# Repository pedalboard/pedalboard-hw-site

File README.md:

# pedalboard-hw-site

Source code for github pages avalilable from https://pedalboard.github.io/pedalboard-hw-site

This is mostly generated. Do not edit directly!

* latest is generated from main
* latest-x is generated from branch x
* vX.Y.Z are the released versions
* stable points to the current stable release

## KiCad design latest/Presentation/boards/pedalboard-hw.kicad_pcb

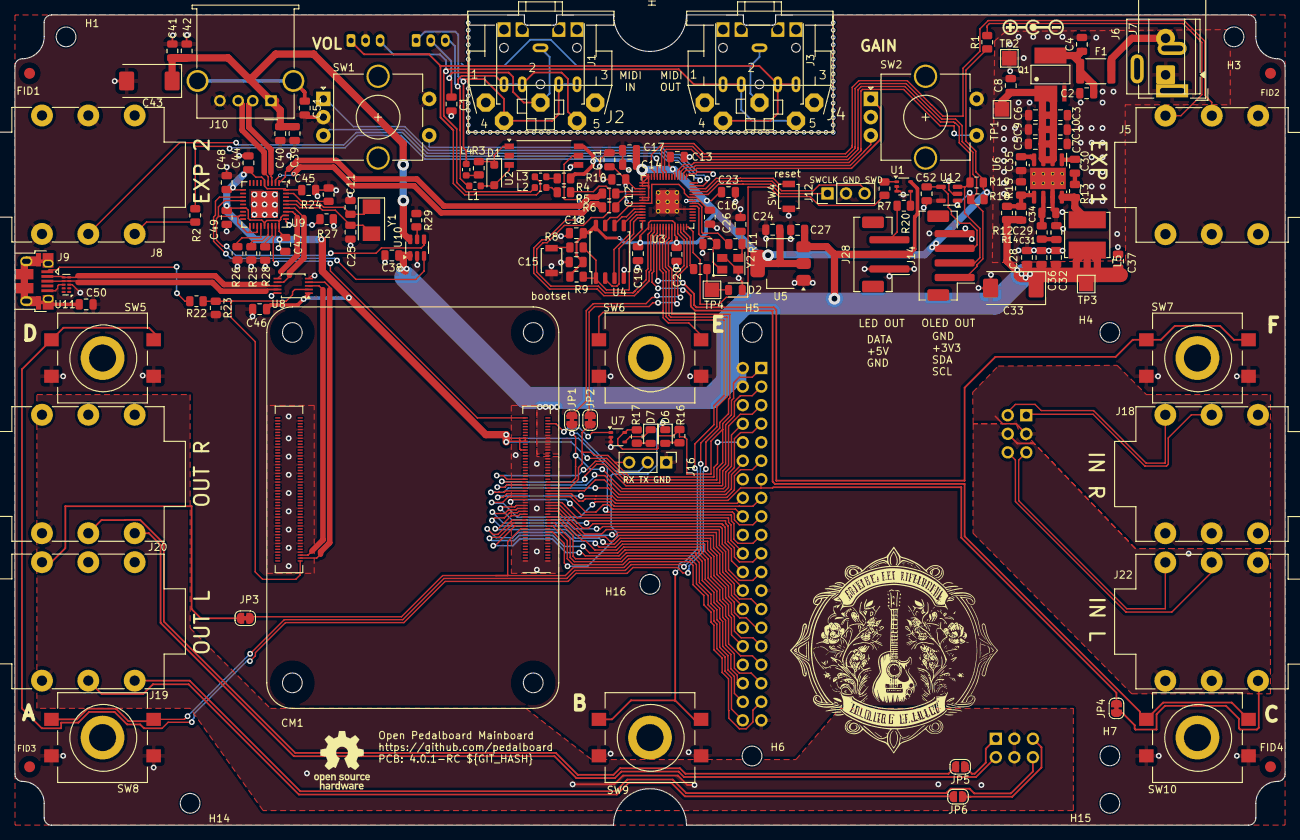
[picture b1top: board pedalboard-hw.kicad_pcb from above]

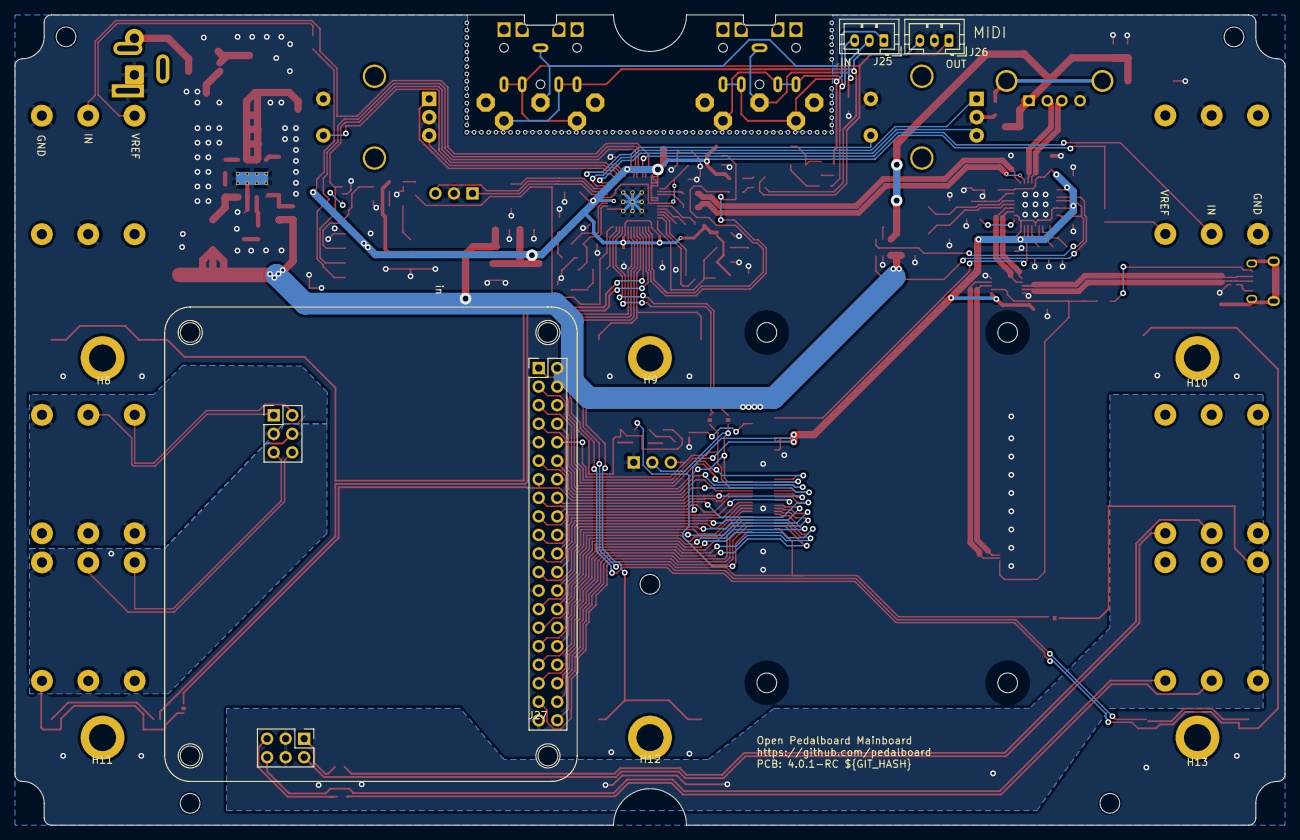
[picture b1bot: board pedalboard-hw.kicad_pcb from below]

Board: 2 copper layers, 174.0 x 111.0 mm, 169 parts (9 on the bottom side), 142 nets.

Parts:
C1, C13, C15, C16, C17, C18, C19, C20, C21, C23, C30, C35, C46, C47, C48, C49, C52: 100n; C_0805_2012Metric
C2, C3, C4, C5, C6, C7, C8, C9, C10, C24, C27, C28, C32, C36, C37, C38, C39, C40, C41, C42, C44, C45: 10u; C_0805_2012Metric
C11, C25: 18p; C_0805_2012Metric
C12, C14: 1u; C_0805_2012Metric
C22, C26: 15p; C_0805_2012Metric
C29, C34, C50, C51: 1n; C_0805_2012Metric
C31: 1.2n; C_0805_2012Metric
C33, C43: 100u; CP_EIA-7343-31_Kemet-D
CM1: CM4; Raspberry-Pi-4-Compute-Module
D1: SM4007; D_SOD-123F
D2, D6: LED Y; LED_0805_2012Metric
D7: LED R; LED_0805_2012Metric
F1: Polyfuse 1.8A; Fuse_1812_4532Metric
FID1, FID2, FID3, FID4: Fiducial; Fiducial_1.5mm_Mask3mm
H1, H3, H4, H5, H6, H7, H14, H15, H16: MountingHole; MountingHole_2.7mm_M2.5_DIN965
H2: Midi Bites; MIDI bites
H8, H9, H10, H11, H12, H13: Spacer; WA-SMSI_M2.5
J1, J3: Jack 3.5mm; Jack_3.5mm_CUI_SJ1-3525N_Horizontal
J2, J4: DIN5; CP-2350
J5, J8, J18, J19, J20, J22: Jack 6.35mm; Jack_6.35mm_Horizontal
J6: Screw_Terminal_01x02; TerminalBlock_Phoenix_MKDS-1,5-2_1x02_P5.00mm_Horizontal
J7: Barrel_Jack_MountingPin; BarrelJack_Wuerth_6941xx301002
J9: USB_OTG; USB_Micro-B_Amphenol_10103594-0001LF_Horizontal
J10: USB_A; USB_A_Molex_67643_Horizontal
J12, J16: Debug; PinHeader_1x03_P2.54mm_Vertical
J14: JST PH 4; JST_PH_B4B-PH-SM4-TB_1x04-1MP_P2.00mm_Vertical
J25, J26: JST PH 3; JST_PH_B3B-PH-K_1x03_P2.00mm_Vertical
J27: Pedalboard Soundcard; Pedalboard_Soundcard
J28: JST PH 3; JST_PH_B3B-PH-SM4-TB_1x03-1MP_P2.00mm_Vertical
JP1, JP2, JP3, JP4: SJP; SolderJumper-2_P1.3mm_Bridged_RoundedPad1.0x1.5mm
JP5, JP6: SJP; SolderJumper-2_P1.3mm_Open_RoundedPad1.0x1.5mm
L1, L2, L3, L4: 120_100MHz; L_0603_1608Metric
L5: SRN6045TA-3R3Y; L_Bourns_SRN6045TA
Q1: FDS4435BZ; SO08-E3
R1, R2, R8, R11, R16: 1K; R_0805_2012Metric
R3, R7, R20: 220R; R_0805_2012Metric
R4: 33R; R_0805_2012Metric
R5, R13: 10R; R_0805_2012Metric
R6, R10: 27R; R_0805_2012Metric
R9: DNF; R_0805_2012Metric
R12, R24: 12K; R_0805_2012Metric
R14: 20K; R_0805_2012Metric
R15, R17, R21, R22, R23: 2K2; R_0805_2012Metric
R18, R19: 3K9; R_0805_2012Metric
R25, R26, R27, R28, R29: 36K; R_0805_2012Metric
SW1, SW2: 24P/R 24mm; RotaryEncoder_Alps_EC11E-Switch_Vertical_H20mm_CircularMoun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
SW3, SW4: Micro Button; SW_SPST_B3U-1000P
SW5, SW6, SW7, SW8, SW9, SW10: Tactile Button; SW_PUSH-12mm_Wuerth
SYM1: Logo_Open_Hardware_Small; OSHW-Logo_7.5x8mm_SilkScreen
TP1, TP2, TP3, TP4: TestPoint; TestPoint_Pad_2.0x2.0mm
U1, U7: 74AHCT1G32SE-7; SOT-353_SC-70-5
U2: TLP2761; SO-6L_10x3.84mm_P1.27mm
U3: RP2040; RP2040-QFN-56
U4: W25Q128JVS; SOIC-8_5.23x5.23mm_P1.27mm
U5: NCP1117-3.3_SOT223; SOT-223-3_TabPin2
U6: AP64501SP-13; SOIC-8-1EP_3.9x4.9mm_P1.27mm_EP2.95x4.9mm_Mask2.71x3.4mm_Th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
U8: FSUSB42MUX; TSSOP-10_3x3mm_P0.5mm
U9: USB2514B_Bi; QFN-36-1EP_6x6mm_P0.5mm_EP3.7x3.7mm
U10: AP2553W6; SOT-23-6
U11: TPD4EUSB30; USON-10_2.5x1.0mm_P0.5mm
U12: AT24CS01-STUM; SOT-23-5
Y1: Crystal_Small; Crystal_SMD_5032-2Pin_5.0x3.2mm
Y2: ABM8-272-T3; ABM8-272-T3_ABR

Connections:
+1V1: C12.1, C16.1, C21.1, U3.23 (DVDD), U3.45 (VREG_VOUT), U3.50 (DVDD)
+3V3: C13.1, C14.1, C15.1, C17.1, C18.1, C19.1, C20.1, C23.1, C24.1, C52.1, J14.3, R1.1, R2.1, R4.1, R9.1, R18.1, R19.1, U2.6 (VDD), U3.1 (IOVDD), U3.10 (IOVDD), U3.22 (IOVDD), U3.33 (IOVDD), U3.42 (IOVDD), U3.43 (ADC_AVDD), U3.44 (VREG_IN), U3.48 (USB_VDD), U3.49 (IOVDD), U4.8 (VCC), U5.2 (VO), U12.4 (VCC)
+5VP: C27.1, C28.1, C29.1, C32.1, C33.1, C36.1, C37.1, C38.1, CM1.77 (+5v_(Input)), CM1.79 (+5v_(Input)), CM1.81 (+5v_(Input)), CM1.83 (+5v_(Input)), CM1.85 (+5v_(Input)), CM1.87 (+5v_(Input)), J27.2 (5V), J27.4 (5V), J28.2, L5.2, R12.1, TP3.1, U1.5 (VCC), U5.3 (VI), U10.1 (IN)
/Audio/CM4_3V: C44.1, C45.1, C46.1, C47.1, C48.1, C49.1, CM1.78 (GPIO_VREF(1.8v/3.3v_Input)), CM1.84 (+3.3v_(Output)), CM1.86 (+3.3v_(Output)), J27.1 (3V3), J27.17 (3V3), R16.2, R17.2, U7.5 (VCC), U8.1 (VCC), U9.5 (VDDA33), U9.10 (VDDA33), U9.15 (VDD33), U9.23 (VDD33), U9.27 (VBUS_DET), U9.29 (VDDA33), U9.36 (VDDA33)
/Audio/CM4_GPIO4: CM1.54 (GPIO4), J27.7 (GCLK0/GPIO4)
/Audio/CM4_GPIO5: CM1.34 (GPIO5), J27.29 (GCLK1/GPIO5)
/Audio/CM4_GPIO6: CM1.30 (GPIO6), J27.31 (GCLK2/GPIO6)
/Audio/CM4_GPIO7: CM1.37 (GPIO7), J27.26 (~CE1/GPIO7)
/Audio/CM4_GPIO8: CM1.39 (GPIO8), J27.24 (~CE0/GPIO8)
/Audio/CM4_GPIO9: CM1.40 (GPIO9), J27.21 (MISO0/GPIO9)
/Audio/CM4_GPIO10: CM1.44 (GPIO10), J27.19 (MOSI0/GPIO10)
/Audio/CM4_GPIO11: CM1.38 (GPIO11), J27.23 (SCLK0/GPIO11)
/Audio/CM4_GPIO12: CM1.31 (GPIO12), J27.32 (PWM0/GPIO12)
/Audio/CM4_GPIO13: CM1.28 (GPIO13), J27.33 (PWM1/GPIO13)
/Audio/CM4_GPIO16: CM1.29 (GPIO16), J27.36 (GPIO16)
/Audio/CM4_GPIO17: CM1.50 (GPIO17), J27.11 (GPIO17)
/Audio/CM4_GPIO22: CM1.46 (GPIO22), J27.15 (GPIO22)
/Audio/CM4_GPIO23: CM1.47 (GPIO23), J27.16 (GPIO23)
/Audio/CM4_GPIO24: CM1.45 (GPIO24), J27.18 (GPIO24)
/Audio/CM4_GPIO25: CM1.41 (GPIO25), J27.22 (GPIO25)
/Audio/CM4_ID_SC: CM1.35 (ID_SC), J27.28 (ID_SC/GPIO1)
/Audio/CM4_ID_SD: CM1.36 (ID_SD), J27.27 (ID_SD/GPIO0)
/Audio/CM4_LED_ACT: CM1.21 (PI_nLED_Activity), D6.1 (K)
/Audio/CM4_LED_PWR: CM1.95 (nPI_LED_PWR), U7.1 (A)
/Audio/GND_in_L: J22.RN, J22.S, J22.TN, J27.44 (in_GND)
/Audio/GND_in_R: J18.RN, J18.S, J18.TN, J27.43 (in_GND)
/Audio/GND_out: J19.S, J20.S, J27.49 (out_GND), J27.50 (out_GND)
/Audio/INT_MIDI_RX: CM1.51 (GPIO15), J16.3, J27.10 (GPIO15/RXD), JP2.1 (A)
/Audio/INT_MIDI_TX: CM1.55 (GPIO14), J16.2, J27.8 (GPIO14/TXD), JP1.1 (A)
/Audio/audio_in_stereo: CM1.48 (GPIO27), J27.13 (GPIO27), JP4.2 (B)
/Audio/audio_out_stereo: CM1.24 (GPIO26), J27.37 (GPIO26), JP3.2 (B)
/Audio/audio_pcm_clk: CM1.49 (GPIO18), J27.12 (GPIO18/PWM0)
/Audio/audio_pcm_din: CM1.27 (GPIO20), J27.38 (GPIO20/MOSI1)
/Audio/audio_pcm_dout: CM1.25 (GPIO21), J27.40 (GPIO21/SCLK1)
/Audio/audio_pcm_fs: CM1.26 (GPIO19), J27.35 (GPIO19/MISO1)
/Audio/conf_i2c_scl: CM1.56 (GPIO3), J27.5 (SCL/GPIO3)
/Audio/conf_i2c_sda: CM1.58 (GPIO2), J27.3 (SDA/GPIO2)
/Audio/in_L+: J22.T, J27.45 (in_L+)
/Audio/in_L-: J22.R, J27.46 (in_L-)
/Audio/in_R+: J18.T, J27.42 (in_R+)
/Audio/in_R-: J18.R, J27.41 (in_R-)
/Audio/nEXTRST: CM1.100 (nEXTRST), U9.26 (RESET_N)
/Connectivity/USB_CM_N: CM1.103 (USB2_N), U8.4 (D-)
/Connectivity/USB_CM_P: CM1.105 (USB2_P), U8.3 (D+)
/Connectivity/USB_D_N: J9.2 (D-), U8.8 (HSD2-), U11.5 (D2-)
/Connectivity/USB_D_P: J9.3 (D+), U8.9 (HSD2+), U11.4 (D2+)
/Connectivity/USB_OUT_N: J10.2 (D-), U9.3 (USBDM_DN2/PRT_DIS_M2)
/Connectivity/USB_OUT_P: J10.3 (D+), U9.4 (USBDP_DN2/PRT_DIS_P2)
/Connectivity/USB_RP_N: R10.1, U9.1 (USBDM_DN1/PRT_DIS_M1)
/Connectivity/USB_RP_P: R6.1, U9.2 (USBDP_DN1/PRT_DIS_P1)
/Connectivity/USB_UP_N: U8.6 (HSD1-), U9.30 (USBDM_UP)
/Connectivity/USB_UP_P: U8.7 (HSD1+), U9.31 (USBDP_UP)
/Connectivity/VBUS: C39.1, C40.1, C41.1, C42.1, C43.1, J10.1 (VBUS), U10.6 (OUT)
/Connectivity/nOCS1: U9.13 (OCS_N1), U9.17 (OCS_N2), U9.19 (OCS_N3), U9.21 (OCS_N4), U10.4 (nFault)
/LEDs/RGB_DATA: R7.1, U3.14 (GPIO11)
/MIDI/A_EXP1: J5.R, U3.40 (GPIO28_ADC2)
/MIDI/A_EXP2: J8.R, U3.39 (GPIO27_ADC1)
/MIDI/EXT_MIDI_RX: U2.5 (VO), U3.3 (GPIO1)
/MIDI/EXT_MIDI_TX: R5.2, U3.2 (GPIO0)
/MIDI/I2C_SCL: J14.1, R18.2, U3.37 (GPIO25), U12.1 (SCL)
/MIDI/I2C_SDA: J14.2, R19.2, U3.36 (GPIO24), U12.3 (SDA)
/MIDI/QSPI_SCLK: U3.52 (QSPI_SCLK), U4.6 (CLK)
/MIDI/QSPI_SD0: U3.53 (QSPI_SD0), U4.5 (DI(IO0))
/MIDI/QSPI_SD1: U3.55 (QSPI_SD1), U4.2 (DO(IO1))
/MIDI/QSPI_SD2: U3.54 (QSPI_SD2), U4.3 (IO2)
/MIDI/QSPI_SD3: U3.51 (QSPI_SD3), U4.7 (IO3)
/MIDI/QSPI_SS: R8.2, R9.2, U3.56 (QSPI_SS), U4.1 (~CS)
/MIDI/ROT_GAIN_A: SW2.A, U3.30 (GPIO19)
/MIDI/ROT_GAIN_B: SW2.B, U3.31 (GPIO20)
/MIDI/ROT_VOL_A: SW1.A, U3.27 (GPIO16)
/MIDI/ROT_VOL_B: SW1.B, U3.28 (GPIO17)
/MIDI/SWCLK: J12.1, U3.24 (SWCLK)
/MIDI/SWD: J12.3, U3.25 (SWD)
/MIDI/SW_A: SW8.1, U3.8 (GPIO6)
/MIDI/SW_B: SW9.1, U3.7 (GPIO5)
/MIDI/SW_C: SW10.1, U3.4 (GPIO2)
/MIDI/SW_D: SW5.1, U3.9 (GPIO7)
/MIDI/SW_E: SW6.1, U3.6 (GPIO4)
/MIDI/SW_F: SW7.1, U3.5 (GPIO3)
/MIDI/SW_GAIN: SW2.S1, U3.32 (GPIO21)
/MIDI/SW_VOL: SW1.S1, U3.29 (GPIO18)
/MIDI/XIN: C22.1, U3.20 (XIN), Y2.1
/MIDI/XOUT: R11.1, U3.21 (XOUT)
/MIDI/~USB_BOOT: R8.1, SW3.2
/Power Supply/fused: C2.1, C4.1, F1.2, Q1.5-8
/Power Supply/polarity_checked: C3.1, C5.1, C6.1, C7.1, C8.1, C9.1, C10.1, Q1.1-3, TP1.1, U6.2 (VIN), U6.3 (EN)
/Power Supply/switch: L5.1, R13.1, U6.8 (SW)
/Power Supply/unfused: F1.1, J6.2, J7.2
GND: C1.2, C2.2, C3.2, C4.2, C5.2, C6.2, C7.2, C8.2, C9.2, C10.2, C11.2, C12.2, C13.2, C14.2, C15.2, C16.2, C17.2, C18.2, C19.2, C20.2, C21.2, C22.2, C23.2, C24.2, C25.2, C26.2, C27.2, C28.2, C31.2, C32.2, C33.2, C34.2, C35.2, C36.2, C37.2, C38.2, C39.2, C40.2, C41.2, C42.2, C43.2, C44.2, C45.2, C46.2, C47.2, C48.2, C49.2, C50.2, C51.2, C52.2, CM1.1 (GND), CM1.2 (GND), CM1.7 (GND), CM1.8 (GND), CM1.13 (GND), CM1.14 (GND), CM1.22 (GND), CM1.23 (GND), CM1.32 (GND), CM1.33 (GND), CM1.42 (GND), CM1.43 (GND), CM1.52 (GND), CM1.53 (GND), CM1.59 (GND), CM1.60 (GND), CM1.65 (GND), CM1.66 (GND), CM1.71 (GND), CM1.74 (GND), CM1.98 (GND), CM1.107 (GND), CM1.108 (GND), CM1.113 (GND), CM1.114 (GND), CM1.119 (GND), CM1.120 (GND), CM1.125 (GND), CM1.126 (GND), CM1.131 (GND), CM1.132 (GND), CM1.137 (GND), CM1.138 (GND), CM1.144 (GND), CM1.150 (GND), CM1.155 (GND), CM1.156 (GND), CM1.161 (GND), CM1.162 (GND), CM1.167 (GND), CM1.168 (GND), CM1.173 (GND), CM1.174 (GND), CM1.179 (GND), CM1.180 (GND), CM1.185 (GND), CM1.186 (GND), CM1.191 (GND), CM1.192 (GND), CM1.197 (GND), CM1.198 (GND), D2.1 (K), J3.S, J4.2, J5.RN, J5.S, J6.1, J7.1, J8.RN, J8.S, J9.5 (GND), J10.4 (GND), J12.2, J14.4, J16.1, J26.2, J27.6 (GND), J27.9 (GND), J27.14 (GND), J27.20 (GND), J27.25 (GND), J27.30 (GND), J27.34 (GND), J27.39 (GND), J28.1, Q1.4, R15.2, R23.2, R24.2, R25.2, R26.2, R27.2, R28.2, R29.1, SW1.C, SW1.S2, SW2.C, SW2.S2, SW3.1, SW4.1, SW5.2, SW6.2, SW7.2, SW8.2, SW9.2, SW10.2, TP2.1, U1.2 (B), U1.3 (GND), U2.4 (GND), U3.19 (TESTEN), U3.57 (GND), U4.4 (GND), U5.1 (GND), U6.7 (GND), U6.9 (EP), U7.2 (B), U7.3 (GND), U8.5 (GND), U8.10 (~OE), U9.37 (VSS), U10.2 (GND), U11.3 (GND), U11.8 (GND), U12.2 (GND), U12.5 (WP), Y2.2, Y2.4
unnamed: C26.1, R11.2, Y2.3
unnamed: C30.1, R13.2
unnamed: C31.1, R14.2
unnamed: CM1.101 (USB_OTG_ID), R22.1, R23.1, U8.2 (SEL)
unnamed: D1.2 (A), L1.2, U2.3 (K)
unnamed: D1.1 (K), R3.2, U2.1 (A)
unnamed: D2.2 (A), R21.2, TP4.1
unnamed: D6.2 (A), R16.1
unnamed: D7.2 (A), R17.1
unnamed: D7.1 (K), U7.4 (Y)
unnamed: J5.T, R1.2
unnamed: J8.T, R2.2
unnamed: C50.1, J9.6 (Shield)
unnamed: J9.1 (VBUS), R22.2
unnamed: C51.1, J10.5 (Shield)
unnamed: J1.R, J1.RN, J2.4, J25.1, L4.1
unnamed: C1.1, J1.S, J2.2, J25.2
unnamed: J1.T, J1.TN, J2.5, J25.3, L1.1
unnamed: J3.R, J3.RN, J4.4, J26.1, L3.1
unnamed: J3.T, J3.TN, J4.5, J26.3, L2.1
unnamed: J19.T, J27.52 (out_L)
unnamed: J20.T, J27.48 (out_R)
unnamed: J28.3, R20.2
unnamed: JP1.2 (B), U3.12 (GPIO9)
unnamed: JP2.2 (B), U3.11 (GPIO8)
unnamed: J19.SN, JP3.1 (A)
unnamed: J22.SN, JP4.1 (A)
unnamed: J27.47 (out_5V), JP5.1 (A)
unnamed: J20.R, JP5.2 (B)
unnamed: J27.51 (out_5V), JP6.1 (A)
unnamed: J19.R, JP6.2 (B)
unnamed: L2.2, R5.1
unnamed: L3.2, R4.2
unnamed: L4.2, R3.1
unnamed: R7.2, U1.1 (A)
unnamed: R20.1, U1.4 (Y)
unnamed: R21.1, U3.13 (GPIO10)
unnamed: SW4.2, U3.26 (RUN)
unnamed: R10.2, U3.46 (USB_DM)
unnamed: R6.2, U3.47 (USB_DP)
unnamed: C30.2, U6.1 (BST)
unnamed: C34.1, R14.1, U6.6 (COMP)
unnamed: C29.2, R12.2, R15.1, U6.5 (FB)
unnamed: C35.1, U6.4 (SS)
unnamed: R28.1, U9.25 (HS_IND/CFG_SEL1)
unnamed: R24.1, U9.35 (RBIAS)
unnamed: R25.1, U9.24 (SCL/SMBCLK/CFG_SEL0)
unnamed: R26.1, U9.22 (SDA/SMBDATA/NON_REM1)
unnamed: R27.1, U9.28 (SUSP_IND/LOCAL_PWR/NON_REM0)
unnamed: C11.1, U9.33 (XTALIN/CLKIN), Y1.1
unnamed: C25.1, U9.32 (XTALOUT), Y1.2
unnamed: U9.12 (PRTPWR1/BC_EN1), U10.3 (EN)
unnamed: R29.2, U10.5 (ILIM)

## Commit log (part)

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2023-03-25 Deploying to main from @ pedalboard/pedalboard-hw@b7276a57e73b2701fb4fa2eb38f01aa9e3c14fc2 🚀
2023-03-25 Deploying to main from @ pedalboard/pedalboard-hw@639997d1b679e1036955def84032755c806fb20f 🚀
2023-03-25 Deploying to main from @ pedalboard/pedalboard-hw@56086551936667513878568351cc5841779f6b46 🚀
2023-03-26 Deploying to main from @ pedalboard/pedalboard-hw@15ebe9c566014c20657a59dc8d9d9dcd22285e68 🚀
2023-03-26 Deploying to main from @ pedalboard/pedalboard-hw@a34e61d286a8c7ebd9e98bef948a5071e2d28e11 🚀
2023-03-26 Deploying to main from @ pedalboard/pedalboard-hw@107eaa5d8d474005d9574e15f9211dfb57529940 🚀
2023-03-26 Deploying to main from @ pedalboard/pedalboard-hw@a51df628d6007057972ae2e18b6811cf6ab369c1 🚀
2023-03-27 Deploying to main from @ pedalboard/pedalboard-hw@b50114df462e431f5aad7a325461e2250139b787 🚀
2023-03-27 Deploying to main from @ pedalboard/pedalboard-hw@db5d59866f92e973602bd13b33e3b662fc3cce74 🚀
2023-03-27 Deploying to main from @ pedalboard/pedalboard-hw@036b89f8aa95cc76506a1c4ec3cc837328a9c6e6 🚀
2023-03-27 Deploying to main from @ pedalboard/pedalboard-hw@bc3196ee1f2e587f970f960ee2b963110b6337e8 🚀
2023-03-27 Deploying to main from @ pedalboard/pedalboard-hw@b922dc899fd18d8a57530ea28e42ac5c204ea467 🚀
2023-03-27 Deploying to main from @ pedalboard/pedalboard-hw@8622c2d88bb911061a918989a73a2722e6dd8cfc 🚀
2023-03-27 Deploying to main from @ pedalboard/pedalboard-hw@2fa5456167c5da260a85135685221f4981907e38 🚀
2023-03-27 Deploying to main from @ pedalboard/pedalboard-hw@1f9a216bd1cde34d69044a2512ae8c5d6109ce74 🚀
2023-03-27 Deploying to main from @ pedalboard/pedalboard-hw@2b002e9fa22997c2d848343d5d58fb313a9dbdab 🚀
2023-03-27 Deploying to main from @ pedalboard/pedalboard-hw@5c5707f5e27d2ebd435852af6b7c544ce596c50b 🚀
2023-03-28 Deploying to main from @ pedalboard/pedalboard-hw@ab1eb47c707f1190d496823fec0d73b2a67ae879 🚀
2023-04-04 Deploying to main from @ pedalboard/pedalboard-hw@fee1a6093424101eaf64ddc4dfdbbfde4b55434f 🚀
2023-04-04 Deploying to main from @ pedalboard/pedalboard-hw@cfde31c41bdef452c6ed6f421b92b87394edbf35 🚀
2023-04-05 Deploying to main from @ pedalboard/pedalboard-hw@f849c1d0f29300a9a1679607f3b9d7c0fa9f5f5f 🚀
2023-04-05 Deploying to main from @ pedalboard/pedalboard-hw@cf1a680a94822b390be0284eadb46a3dacae5ada 🚀
2023-04-06 Deploying to main from @ pedalboard/pedalboard-hw@6e9ebe029477b5654b9d176d0dffbacfb02c33a4 🚀
2023-04-07 Deploying to main from @ pedalboard/pedalboard-hw@21c7d4732b43b4d3e347ca5fe547c2fa612cb327 🚀
2023-04-07 Deploying to main from @ pedalboard/pedalboard-hw@a0b7461ff87a92d21607da9c6275ec9f67cfaaa0 🚀
2023-04-07 Deploying to main from @ pedalboard/pedalboard-hw@6d01424e469efda87abd38c5be86be76e11475e6 🚀
2023-04-15 Deploying to main from @ pedalboard/pedalboard-hw@acd08ccde3e564005fafa364f42521e19e73ad6b 🚀
2023-04-15 Deploying to main from @ pedalboard/pedalboard-hw@5949c402c5f4cc4ae07c4ac612c1f53ef18ab881 🚀
2023-04-16 Deploying to main from @ pedalboard/pedalboard-hw@7a98c0943bab17faa8a58335fede2286062115ea 🚀
2023-05-13 Deploying to main from @ pedalboard/pedalboard-hw@170cbd0bfcbc7bc8720f61e222077797f06efb70 🚀
2023-06-05 Deploying to main from @ pedalboard/pedalboard-hw@3f1ebefe3c00ee0aaf6b42aba8ae8e9e593b21a3 🚀
2023-06-12 Deploying to main from @ pedalboard/pedalboard-hw@e5364ac2dec5f234752869372469cf630962c8e1 🚀
2023-07-09 Deploying to main from @ pedalboard/pedalboard-hw@9fa64109e6f198db5dd7bff9b4a6257a63a77d4c 🚀
2023-09-09 Deploying to main from @ pedalboard/pedalboard-hw@d2d4a34964746bc5a78dd8214c9f7561b88935d0 🚀
2023-09-10 Deploying to main from @ pedalboard/pedalboard-hw@07bb7b7d0296cf0ecf3347f2f5c02306554c12c2 🚀
2023-09-10 Deploying to main from @ pedalboard/pedalboard-hw@6bd310da85fdb499219b7cb992151f9b07f65a4b 🚀
2023-09-10 Deploying to main from @ pedalboard/pedalboard-hw@a5a114884279e8929d06e7029135f2d436c421e7 🚀
2023-09-10 Add released documtation versions
2023-09-10 Add a link for backwards compatiblity
2023-09-10 Fix redirect (for OSHWA certification)
2023-09-10 Add link to README
2023-09-10 Deploying to main from @ pedalboard/pedalboard-hw@fa0becf77209d5cf83125339f2ba263d2c88d564 🚀
2023-10-09 Deploying to main from @ pedalboard/pedalboard-hw@f46bf7f8120641a10925b44c016f65dafae1ae81 🚀
2023-10-12 Deploying to main from @ pedalboard/pedalboard-hw@bf0733fa56a0742459f7ed258e7de0835b224bcc 🚀
2023-10-12 Deploying to main from @ pedalboard/pedalboard-hw@96e46e691179b8a0574254d56b19aa1f2bde020a 🚀
2023-10-12 Deploying to main from @ pedalboard/pedalboard-hw@b9b8013d3da3984eae1169d87804db94f22e76ae 🚀
2023-10-12 Deploying to main from @ pedalboard/pedalboard-hw@4a4a5372eb44b9910d373fb1e6795a743f84af02 🚀
2023-10-12 Deploying to main from @ pedalboard/pedalboard-hw@86b9970f5b4ba908b8a9c28b8200e551dac53e3b 🚀
2023-10-12 Deploying to main from @ pedalboard/pedalboard-hw@f646eb87ac38b62818230833db5f05208eea1294 🚀
2023-10-13 Deploying to main from @ pedalboard/pedalboard-hw@5b3653b2e23504b5c5f70041b2f958eefcc25ef6 🚀
2023-10-13 Deploying to main from @ pedalboard/pedalboard-hw@5c6320140fc33604beedab7a0804e45f52e10822 🚀
2023-10-13 Deploying to main from @ pedalboard/pedalboard-hw@c5bffb9d33541774c2d8d28a1eb68f16a20c8530 🚀
2023-10-14 Deploying to main from @ pedalboard/pedalboard-hw@7f5d17fece31c741eafc27f5ef563d22e5f8b4ae 🚀
2023-10-14 Deploying to main from @ pedalboard/pedalboard-hw@6154ac0ac97e24e7d36d42cc245025ec99c802b7 🚀
2023-10-16 Deploying to main from @ pedalboard/pedalboard-hw@329373046230eb90cfac6330b5614748efeb6bbd 🚀
2023-10-16 Deploying to main from @ pedalboard/pedalboard-hw@a96f2fbf929ec68e717437c5ed47ad4064755ab0 🚀
2023-10-17 Deploying to main from @ pedalboard/pedalboard-hw@1e6d981355dcc15d5b569c6dd3e0631d1ab0b030 🚀
2023-10-19 Deploying to main from @ pedalboard/pedalboard-hw@99cd66b43a203ee2ef2d541e2dd5a92a72f15cb0 🚀
2023-10-19 Deploying to main from @ pedalboard/pedalboard-hw@5e40ce46acd865abdfefbedd590a57e852965475 🚀
2023-10-19 Deploying to main from @ pedalboard/pedalboard-hw@b1052275dee0ef88fe026b24eea4cdda36d7439d 🚀
2023-10-19 Deploying to main from @ pedalboard/pedalboard-hw@1327b095618eb31e28da54afeec1b97277f4410a 🚀
2023-10-19 Version 3.0.0 assets
2023-10-20 Remove unused version
2023-10-20 Deploying to main from @ pedalboard/pedalboard-hw@f44750be3d099d6bb03b820817c33e3d70e13b71 🚀
2023-10-22 Deploying to main from @ pedalboard/pedalboard-hw@f7a608bfef67fd92f83c4251e1fcd6851bb4855a 🚀
2023-10-22 Deploying to main from @ pedalboard/pedalboard-hw@d1aaf9f5d30e9911c3d3a2474d1a04eb677c0626 🚀
2023-10-22 Deploying to main from @ pedalboard/pedalboard-hw@ecd8449ab16d2c7a22ae6d517a1b5c002c852a43 🚀
2023-10-22 Deploying to main from @ pedalboard/pedalboard-hw@1ae6acf7456985267f537341a8411b72c3d28aba 🚀
2023-10-22 Deploying to main from @ pedalboard/pedalboard-hw@00482a1aaf123f81a0cb75651b7e9fcf10cc6686 🚀
2023-10-22 Deploying to main from @ pedalboard/pedalboard-hw@f8d88dcd29c7265fc0a7cae16b73048a00413a6a 🚀
2023-10-23 Deploying to main from @ pedalboard/pedalboard-hw@6563da8361bd266bf2d9257b45dde79b4e4e8acc 🚀
2023-10-23 Deploying to main from @ pedalboard/pedalboard-hw@bc87760d1f9e8282b593f46d3dc0dc00412ce085 🚀
2023-10-23 Deploying to main from @ pedalboard/pedalboard-hw@56e9e9112f2c2b04a2ad7c682bbaf6328fe51617 🚀
2023-11-26 Deploying to main from @ pedalboard/pedalboard-hw@1dd28d15906509df27e55f3f9d711ac8a4212e40 🚀
2023-11-29 Deploying to main from @ pedalboard/pedalboard-hw@8c8f0d09d0cef5fbd01a28cda44a208598a17f6f 🚀
2023-12-02 Deploying to main from @ pedalboard/pedalboard-hw@0b94282338685e23d187a9ec0f06ddb9b3b0cfea 🚀
2023-12-02 Deploying to main from @ pedalboard/pedalboard-hw@fdadf182ddd40056f5c67751a223948ec78c10db 🚀
2023-12-02 Deploying to main from @ pedalboard/pedalboard-hw@d17e227001aed1fdd2b0ca74bcede5b0c660dd07 🚀
2023-12-02 Deploying to main from @ pedalboard/pedalboard-hw@0edb0cb26a37e28591dca158c81390d0ae3dad52 🚀
2023-12-03 Deploying to main from @ pedalboard/pedalboard-hw@603f5830fc04b6f7624dab7a2b4d34798a719d09 🚀
2023-12-03 Deploying to main from @ pedalboard/pedalboard-hw@3a46acdcf6842481d0e6d8c3cf227623d50a708c 🚀
2023-12-03 Deploying to main from @ pedalboard/pedalboard-hw@b8af2059fa4f4e8d13dae25528e4c9b414cbee45 🚀
2023-12-03 Deploying to main from @ pedalboard/pedalboard-hw@71cc22228b63dacac1e99c41e951aad9e4d50dc7 🚀
2023-12-03 Deploying to main from @ pedalboard/pedalboard-hw@9312d4046c6ada6c3ba7f5d648b6e23612b2f376 🚀
2023-12-04 Deploying to main from @ pedalboard/pedalboard-hw@813dae4b1dd0d9e702ef2d3e113875ef7000f311 🚀
2023-12-04 Deploying to main from @ pedalboard/pedalboard-hw@57e0efd8a907f6c02b7c1aca78c280200fc38051 🚀
2023-12-04 Deploying to main from @ pedalboard/pedalboard-hw@2870e3ca46bb9a72af779705dc9f47d1a8fde212 🚀
2023-12-04 Deploying to main from @ pedalboard/pedalboard-hw@cac37567d87130e1f1fd55058c741824c7c66eca 🚀
2023-12-04 Deploying to main from @ pedalboard/pedalboard-hw@824524a38e74db77429721b2f1cec58040449eae 🚀
2023-12-04 Deploying to main from @ pedalboard/pedalboard-hw@46b11b049da54ac753e95788430fed91afcccbab 🚀
2023-12-04 v3.1.0 content
2023-12-05 Deploying to main from @ pedalboard/pedalboard-hw@972132c831802e29eda158218c470368f4d5a959 🚀
2023-12-05 v3.1.1 content
2023-12-27 Deploying to main from @ pedalboard/pedalboard-hw@7c19d6f6888c9c247cd9fd8cdbd36559c2e37af3 🚀
2024-01-07 Deploying to main from @ pedalboard/pedalboard-hw@0d11d3c9b16d3de2d81ad4268e4ba8ca2e206dbf 🚀
2024-01-07 Deploying to main from @ pedalboard/pedalboard-hw@f301a5e9d7f9c574fdc6aa64b48fad876563c769 🚀
2024-01-07 Deploying to main from @ pedalboard/pedalboard-hw@e17b1b071623a306ca5a1bdb915c06f00f050a4a 🚀
2024-01-07 Deploying to main from @ pedalboard/pedalboard-hw@9d8679a68fdf8c5f7f2b36d3f7b295776def8d4b 🚀
2024-01-07 Deploying to main from @ pedalboard/pedalboard-hw@9f26bfbdac674d52c2dd905373fbb87f02c0f916 🚀
2024-10-09 Deploying to main from @ pedalboard/pedalboard-hw@5b92df5a6c086741117cc0d23b220d533705950c 🚀
2024-10-09 Deploying to main from @ pedalboard/pedalboard-hw@5b819b5ecd7a2f87476d7c3a695441b1ba8d3780 🚀
2024-10-10 Deploying to main from @ pedalboard/pedalboard-hw@05152415455b7d306b7d9ddb62e82a8d0f253708 🚀
2024-10-10 Deploying to main from @ pedalboard/pedalboard-hw@6f83c29f9d913721a44b7624e2a8a8f30e33f92f 🚀
2024-10-13 Deploying to main from @ pedalboard/pedalboard-hw@ec2cf5a4450f57a3e93c2f13b006314181f0e247 🚀
2024-10-13 Deploying to main from @ pedalboard/pedalboard-hw@2444a6fdf065345652d68f1a9c6656906ab7ed84 🚀
2024-10-14 Deploying to main from @ pedalboard/pedalboard-hw@9a106b7afa6b11f1b0b0d0594b1e593bc2ad20a8 🚀
2024-10-14 Deploying to main from @ pedalboard/pedalboard-hw@12cc672e68b075266669d4db86791a5a544596b0 🚀
2024-10-14 Deploying to main from @ pedalboard/pedalboard-hw@ae3fd9677071b57de4a15d2ca74697a33b5d8b55 🚀
2024-10-15 Deploying to main from @ pedalboard/pedalboard-hw@19e8535726449e064b60469e68455b50c1a73f74 🚀
2024-10-15 Deploying to main from @ pedalboard/pedalboard-hw@fac257e563c0b379400492d2ebe1d85ca050e676 🚀
2024-10-15 Deploying to main from @ pedalboard/pedalboard-hw@ea7c8fbe5909aa9282b6f77317e5cba65e6902d7 🚀
2024-10-15 Deploying to main from @ pedalboard/pedalboard-hw@7a1c44809771adda5929f8b8b3580cf41bb84aa1 🚀
2024-10-15 Deploying to main from @ pedalboard/pedalboard-hw@abca3e42c0fdb83021ac3eeb8d465bf6e8b5db48 🚀
2024-10-16 Deploying to main from @ pedalboard/pedalboard-hw@31311c74dc1991e99ccf6e6ef67460cf9ac0685e 🚀
2024-10-16 Deploying to main from @ pedalboard/pedalboard-hw@62821116d90ae0413fa60c0887e567ca53675119 🚀
2024-10-16 Deploying to main from @ pedalboard/pedalboard-hw@09ba678ee15aa8f3b83aedabc4c1cf882f1a8443 🚀
2024-10-16 Deploying to main from @ pedalboard/pedalboard-hw@9536a5d6d199cdcf598e0fcaa5a09584834b8591 🚀
2024-10-16 v4.0.0
2024-10-17 Deploying to main from @ pedalboard/pedalboard-hw@fbe611ef6f15897fcf52f9e1315d2338af62ff63 🚀
2024-12-15 Deploying to main from @ pedalboard/pedalboard-hw@ee8339fefc6786ae326037750536d855a78fbc5a 🚀
2024-12-16 Deploying to main from @ pedalboard/pedalboard-hw@0c650dedf9a46155597ddb15a88cf017d2a00b00 🚀

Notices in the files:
latest/Presentation/boards/pedalboard-hw.kicad_pcb:
License: CERN Open Hardware Licence Version 2 - Permissive
